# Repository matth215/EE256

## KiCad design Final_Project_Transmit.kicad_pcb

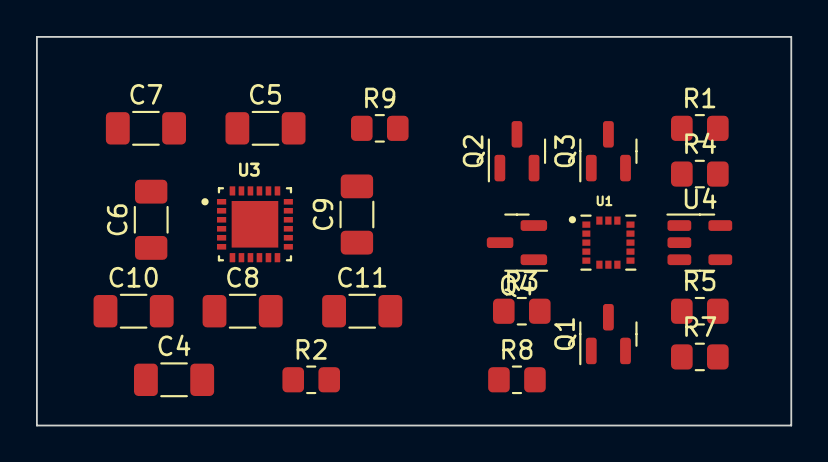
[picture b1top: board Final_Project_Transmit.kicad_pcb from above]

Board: 2 copper layers, 41.9 x 21.6 mm, 23 parts (0 on the bottom side), 16 nets, no tracks yet.

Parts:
C4: 8.2pF; C_1206_3216Metric_Pad1.33x1.80mm_HandSolder
C5, C6, C10: 100nF; C_1206_3216Metric_Pad1.33x1.80mm_HandSolder
C7, C8, C9, C11: 10nF; C_1206_3216Metric_Pad1.33x1.80mm_HandSolder
Q1, Q2, Q3, Q4: BSS138; SOT-23
R1, R3, R4, R5, R7, R8, R9: 10K; R_0805_2012Metric_Pad1.20x1.40mm_HandSolder
R2: 6.1K; R_0805_2012Metric_Pad1.20x1.40mm_HandSolder
U1: LIS3DHTR; XDCR_LIS3DHTR
U3: QFN50P400X400X100-25N
U4: AP2112K-3.3; SOT-23-5

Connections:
+1V5: C9.2, Q1.1 (G), Q2.1 (G), Q3.3 (D), Q4.1 (G), R3.1, U3.4 (V_DDB)
+3V3: Q3.2 (S), U1.1 (VDDIO), U1.14 (VDD), U4.5 (VOUT)
/SDA_3V: Q1.2 (S), U1.6 (SDA)
/SDO: Q4.3 (D), U1.7 (SDO)
GND: C5.2, C6.1, C8.2, C9.1, C10.2, C11.2, U1.5 (GND@1), U1.8 (CS), U1.10 (RES(GND)), U1.12 (GND@2), U3.14 (TST2), U3.16 (TST1), U3.25 (V_SS), U4.2 (GND)
unnamed: Q1.3 (D), U3.12 (P1.0/SPI_SIMO)
unnamed: Q2.3 (D), U3.9 (P1.2/SPI_STE...)
unnamed: Q2.2 (S), U1.4 (SCL)
unnamed: Q4.2 (S), U3.11 (P1.1/SPI_SOMI...)
unnamed: C7.2, U3.5 (CP1)
unnamed: C7.1, U3.6 (CP2)
unnamed: C10.1, U3.7 (V_DD2X)
unnamed: C5.1, U3.24 (V_DDD)
unnamed: C6.2, U3.23 (V_DDH)
unnamed: C8.1, U3.3 (V_DDSW)
VCC: U4.1 (VIN), U4.3 (EN)

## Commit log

2023-10-13 Requirements for Embedded Accelerometer
    My first git upload
2023-11-02 Add files via upload
    Version 1 - needs refinement
2023-11-06 Uploaded V1.1 transmit schematics and pcbs
2023-11-14 Create build files
2023-11-14 Create Fabrication
